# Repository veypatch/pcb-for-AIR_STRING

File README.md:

# AIR_STRING pcb
pcb for air string from chuni arcade

fork: just cleaned up the pcb

## Information
this pcb is designed based on CrazyRedMachine's chunithmIO

that site <https://github.com/CrazyRedMachine/ChunithmIO>

## Pin Out
if u order the pcbs i designed, you need to change the code

check the pin and change them

|PCB|Ardunio|
|:-:|:-----:|
|out1|4|
|out2|5|
|out3|6|
|out4|7|
|out5|8|
|out6|9|
|Dat1|18|
|Dat2|19|

## Parts Required
- 1x arduino pro micro
- 2x any 12x1 pin header socket(2.54mm)
- 4x B6B-XH-A(jst)
- 2x b3b-XH-A(jst)
- 1x b2b-XH-A(jst)

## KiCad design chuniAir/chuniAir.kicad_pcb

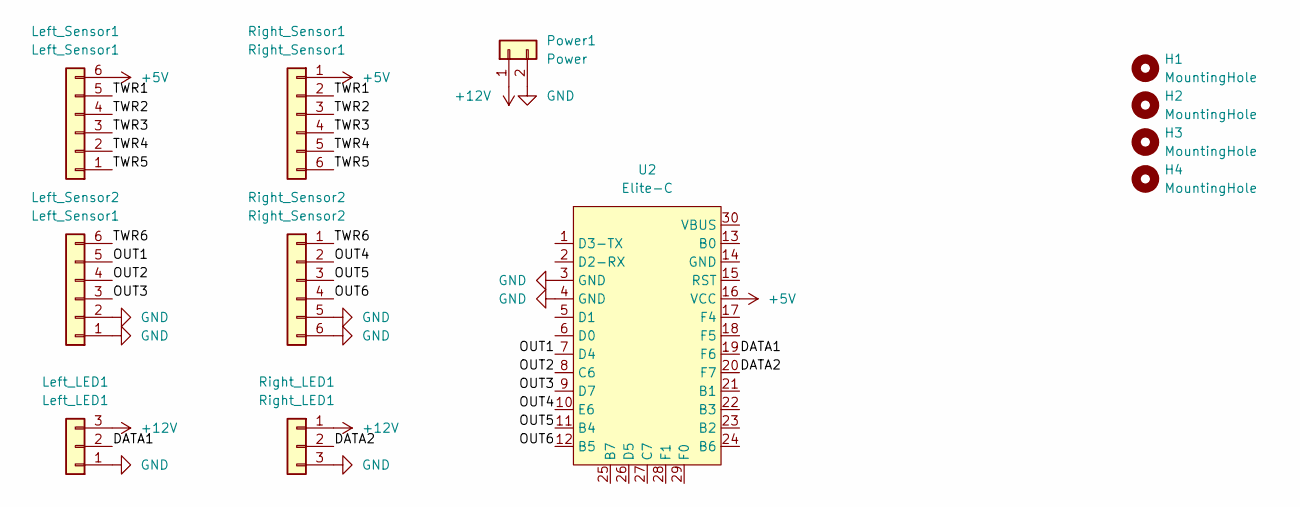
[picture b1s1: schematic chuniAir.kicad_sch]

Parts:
H1, H2, H3, H4: MountingHole; MountingHole_4.3mm_M4
Left_LED1: Left_LED1; JST_XH_B3B-XH-A_1x03_P2.50mm_Vertical
Left_Sensor1, Left_Sensor2: Left_Sensor1; JST_XH_B6B-XH-A_1x06_P2.50mm_Vertical
Power1: Power; JST_XH_B2B-XH-A_1x02_P2.50mm_Vertical
Right_LED1: Right_LED1; JST_XH_B3B-XH-A_1x03_P2.50mm_Vertical
Right_Sensor1: Right_Sensor1; JST_XH_B6B-XH-A_1x06_P2.50mm_Vertical
Right_Sensor2: Right_Sensor2; JST_XH_B6B-XH-A_1x06_P2.50mm_Vertical
U2: Elite-C; Elite-C_ACH

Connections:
+5V: Left_Sensor1.6, Right_Sensor1.1, U2.16 (VCC)
+12V: Left_LED1.3, Power1.1, Right_LED1.1
/DATA1: Left_LED1.2, U2.19 (F6)
/DATA2: Right_LED1.2, U2.20 (F7)
/OUT1: Left_Sensor2.5, U2.7 (D4)
/OUT2: Left_Sensor2.4, U2.8 (C6)
/OUT3: Left_Sensor2.3, U2.9 (D7)
/OUT4: Right_Sensor2.2, U2.10 (E6)
/OUT5: Right_Sensor2.3, U2.11 (B4)
/OUT6: Right_Sensor2.4, U2.12 (B5)
/TWR1: Left_Sensor1.5, Right_Sensor1.2
/TWR2: Left_Sensor1.4, Right_Sensor1.3
/TWR3: Left_Sensor1.3, Right_Sensor1.4
/TWR4: Left_Sensor1.2, Right_Sensor1.5
/TWR5: Left_Sensor1.1, Right_Sensor1.6
/TWR6: Left_Sensor2.6, Right_Sensor2.1
GND: Left_LED1.1, Left_Sensor2.1, Left_Sensor2.2, Power1.2, Right_LED1.3, Right_Sensor2.5, Right_Sensor2.6, U2.3 (GND), U2.4 (GND)

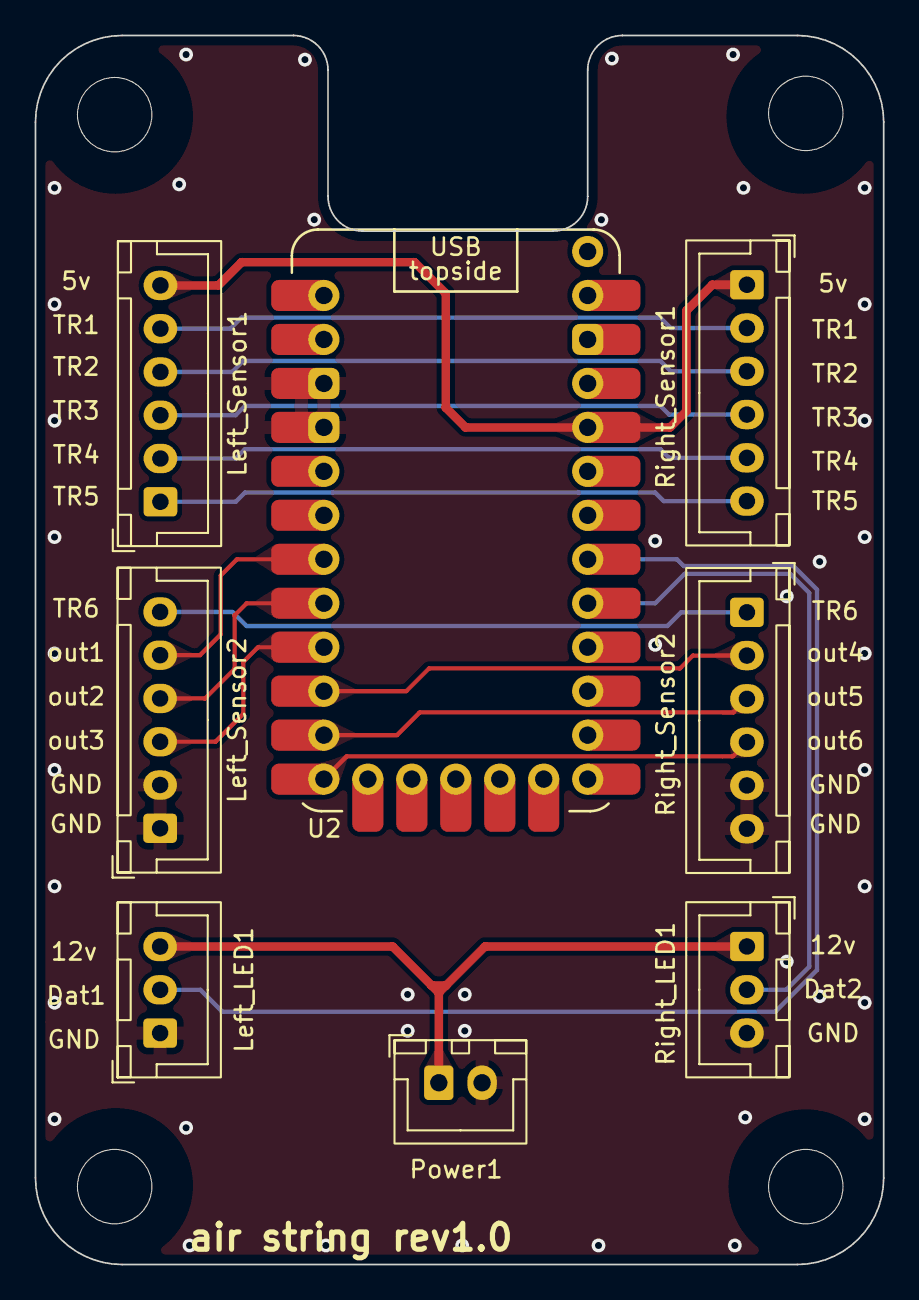
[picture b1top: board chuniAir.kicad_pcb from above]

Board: 2 copper layers, 49.0 x 71.0 mm, 12 parts (0 on the bottom side), 17 nets.

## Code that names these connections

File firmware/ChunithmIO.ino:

#include <FastLED.h>
#include <Keyboard.h>
#define LEFT_PIN 19
#define RIGHT_PIN 18
#define NUM_LEDS 3
#define OUT1 4
#define OUT2 5
#define OUT3 6
#define OUT4 7
#define OUT5 8
#define OUT6 9

CRGB left_leds[NUM_LEDS];
CRGB right_leds[NUM_LEDS];

void setup() {
  Keyboard.begin();
  FastLED.addLeds<WS2811, LEFT_PIN, RGB>(left_leds, NUM_LEDS)
      .setCorrection(TypicalLEDStrip);
  FastLED.addLeds<WS2811, RIGHT_PIN, RGB>(right_leds, NUM_LEDS)
      .setCorrection(TypicalLEDStrip);
  FastLED.setBrightness(64);
  delay(1000);
  fill_solid(left_leds, NUM_LEDS, CRGB(0x7F, 0, 0x23));
  fill_solid(right_leds, NUM_LEDS, CRGB(0x7F, 0, 0x23));
  FastLED.show();
  pinMode(OUT1, INPUT_PULLUP);
  pinMode(OUT2, INPUT_PULLUP);
  pinMode(OUT3, INPUT_PULLUP);
  pinMode(OUT4, INPUT_PULLUP);
  pinMode(OUT5, INPUT_PULLUP);
  pinMode(OUT6, INPUT_PULLUP);
  delay(1000);
}

void loop() {
  if (digitalRead(OUT1) == HIGH) {
    Keyboard.press('a');
  } else {
    Keyboard.release('a');
  }
  if (digitalRead(OUT4) == HIGH) {
    Keyboard.press('b');
  } else {
    Keyboard.release('b');
  }
  if (digitalRead(OUT2) == HIGH) {
    Keyboard.press('c');
  } else {
    Keyboard.release('c');
  }
  if (digitalRead(OUT5) == HIGH) {
    Keyboard.press('d');
  } else {
    Keyboard.release('d');
  }
  if (digitalRead(OUT3) == HIGH) {
    Keyboard.press('e');
  } else {
    Keyboard.release('e');
  }
  if (digitalRead(OUT6) == HIGH) {
    Keyboard.press('f');
  } else {
    Keyboard.release('f');
  }
}
